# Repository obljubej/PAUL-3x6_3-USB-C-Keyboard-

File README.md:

# Paul - Custom Split Keyboard

This project contains the PCB and Gerber files for a custom split keyboard, designed from the ground up using **KiCad** and **Ergogen**. Paul is a 42-key reversible PCB layout, tailored for ergonomic and customizable typing experiences. I currently use this keyboard as my primary device, and it has been a rewarding project from both a hardware and software perspective.

## Features
- **42-Key Reversible PCB Layout**: Designed to be efficient and minimal, the PCB supports both left and right halves of the split keyboard.
- **Custom Key Mapping Software**: Programmed using **QMK-MSYS**, **C++**, and **Python** for full customization of key mappings.
- **OLED Display**: Includes an OLED screen for additional visual feedback.
- **TRRS Jacks**: Easy connectivity between the two halves via TRRS jacks.
- **Fully Customizable Keycaps and Switches**: Tailored for your preferences.

## Hardware
- **PCB Design**: Created using **KiCad** and **Ergogen**, the PCB is compact and optimized for ergonomic usage.
- **Components Soldered**:
  - Resistors
  - Transistors
  - OLED Screen
  - TRRS Jacks
  - Keycaps
- **3D-Printed Case**: Designed and printed custom cases to house the PCB.

## Software
The keyboard firmware was developed using **Visual Studio** and leverages **QMK** for advanced key remapping and functionality. Here are some key details:
- **QMK-MSYS**: The keyboard firmware is programmable through QMK, allowing for endless customization of the key layout.
- **C++ and Python**: Used in conjunction with QMK for configuring macros, lighting, and OLED display outputs.

## PCB and Gerber Files
All the files necessary to fabricate your own Paul split keyboard are located in the `pcb/` directory of this repository.

## Getting Started
1. **Download the Gerber Files**: These are necessary for manufacturing the PCB. You can upload these files to any PCB manufacturer of your choice.
2. **Solder the Components**: Refer to the provided PCB design for where to solder the resistors, transistors, OLED screens, TRRS jacks, and key switches.
3. **Flash the Firmware**: Once the PCB is assembled, use QMK to program the firmware. Follow the instructions in the [QMK documentation](https://docs.qmk.fm/#/newbs) to get started with flashing.
4. **Assemble the Keyboard**: Use the provided 3D models to print a case that houses your keyboard and secures the components.

## Usage
This keyboard is fully customizable, and you can program custom keymaps to fit your workflow. Paul is currently in use as my daily keyboard, demonstrating its durability and functionality.

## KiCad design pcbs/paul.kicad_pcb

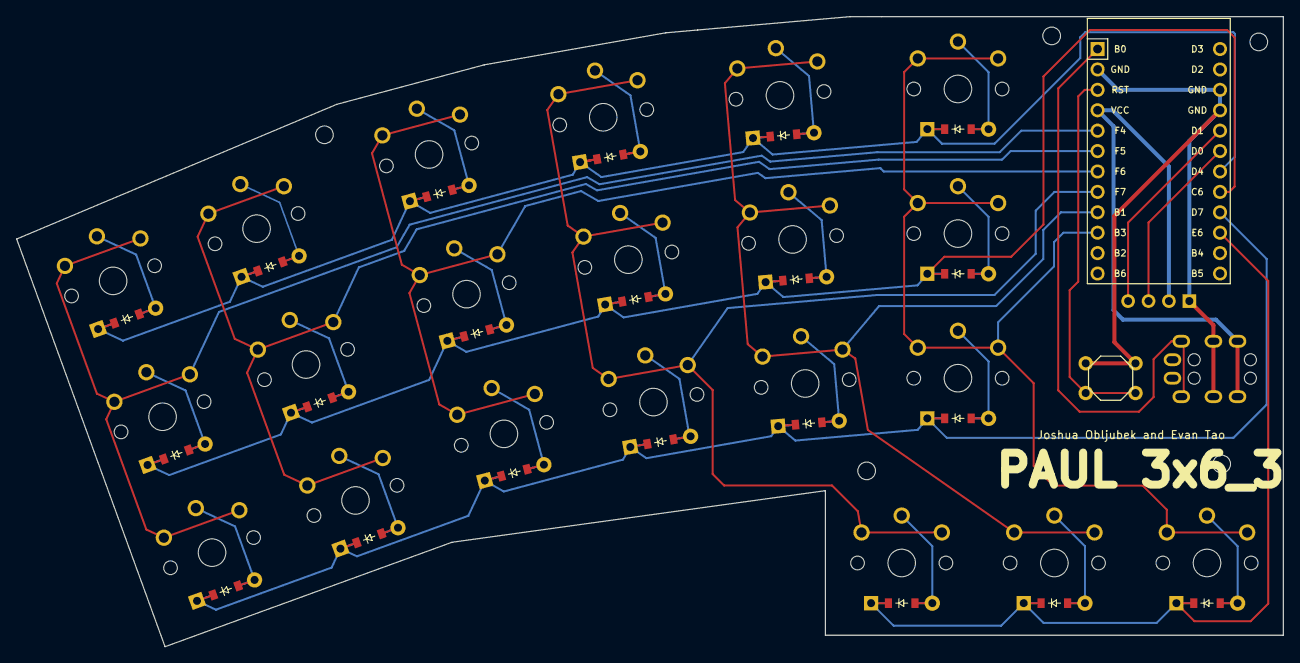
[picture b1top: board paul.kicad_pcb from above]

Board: 2 copper layers, 157.7 x 78.4 mm, 46 parts (0 on the bottom side), 37 nets.

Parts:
B1: SW_TACT_ALPS_SKQGABE010
D1, D2, D3, D4, D5, D6, D7, D8, D9, D10, D11, D12, D13, D14, D15, D16, D17, D18, D19, D20, D21: ComboDiode
MCU1: ProMicro
OLED1: OLED; OLED_headers
S1, S2, S3, S4, S5, S6, S7, S8, S9, S10, S11, S12, S13, S14, S15, S16, S17, S18, S19, S20, S21: PG1350
TRRS1: TRRS-PJ-320A-dual

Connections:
B0: MCU1.1, TRRS1.2
B1: MCU1.9, S13.1, S14.1, S15.1, S20.1
B3: MCU1.10, S16.1, S17.1, S18.1, S21.1
C6: D2.1, D5.1, D8.1, D11.1, D14.1, D17.1, MCU1.20
D0: MCU1.18, OLED1.3
D1: MCU1.17, OLED1.4
D4: D3.1, D6.1, D9.1, D12.1, D15.1, D18.1, MCU1.19
D7: D1.1, D4.1, D7.1, D10.1, D13.1, D16.1, MCU1.21
E6: D19.1, D20.1, D21.1, MCU1.22
F4: MCU1.5, S1.1, S2.1, S3.1
F5: MCU1.6, S4.1, S5.1, S6.1
F6: MCU1.7, S7.1, S8.1, S9.1
F7: MCU1.8, S10.1, S11.1, S12.1, S19.1
GND: B1.1, MCU1.2, MCU1.15, MCU1.16, OLED1.1, TRRS1.1, TRRS1.3
RST: B1.2, MCU1.3
VCC: MCU1.4, OLED1.2, TRRS1.4
farPinky_bottom: D1.2, S1.2
farPinky_home: D2.2, S2.2
farPinky_top: D3.2, S3.2
far_thumb: D21.2, S21.2
home_thumb: D20.2, S20.2
index_bottom: D13.2, S13.2
index_home: D14.2, S14.2
index_top: D15.2, S15.2
inner_bottom: D16.2, S16.2
inner_home: D17.2, S17.2
inner_top: D18.2, S18.2
middle_bottom: D10.2, S10.2
middle_home: D11.2, S11.2
middle_top: D12.2, S12.2
near_thumb: D19.2, S19.2
pinky_bottom: D4.2, S4.2
pinky_home: D5.2, S5.2
pinky_top: D6.2, S6.2
ring_bottom: D7.2, S7.2
ring_home: D8.2, S8.2
ring_top: D9.2, S9.2
